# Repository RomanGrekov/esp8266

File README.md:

# ESPboard - esp8266 based home atomation board

Contain next functions:
  1. Get temperature and relative humidity from DHT22 sensor
  2. Manage GPIO port to turn/off solid state relay
  3. Send and receive data with mqtt protocol.

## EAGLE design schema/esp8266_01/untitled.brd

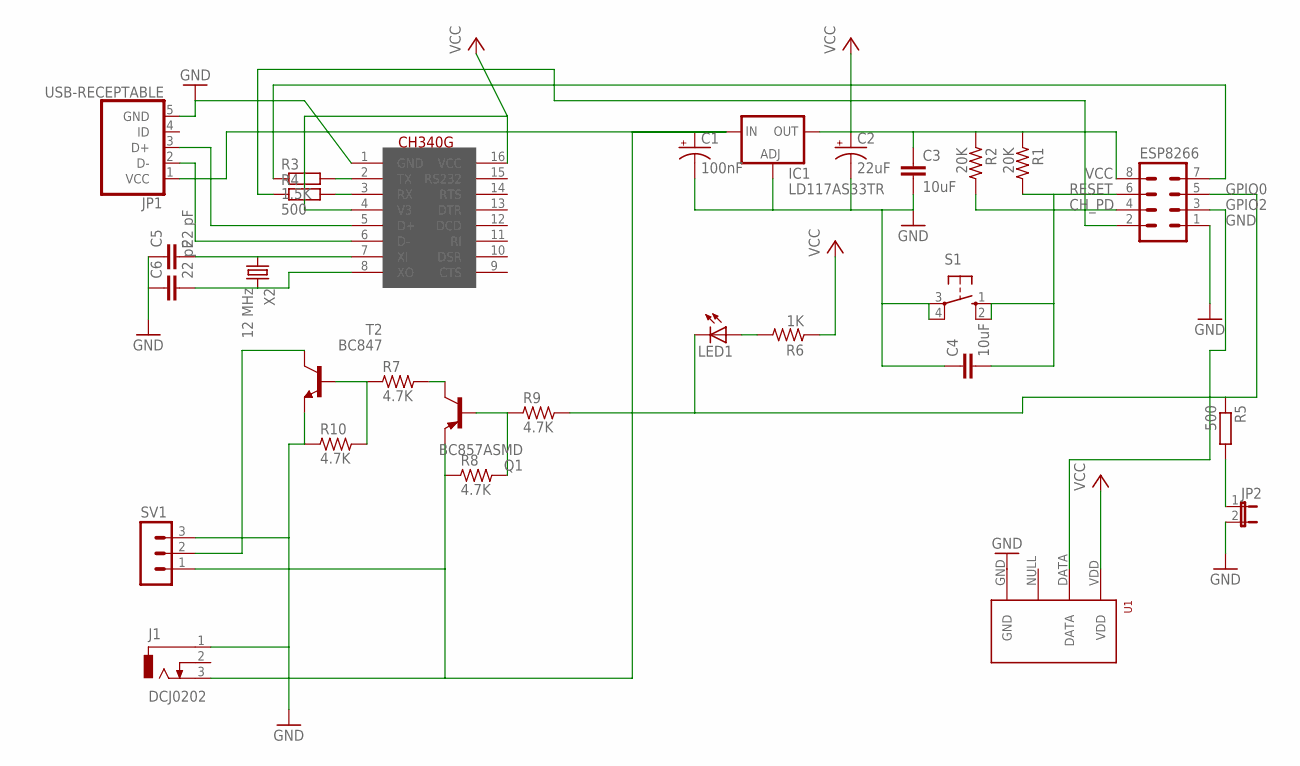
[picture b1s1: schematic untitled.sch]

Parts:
C1: 100nF; E2-4
C2: 22uF; E2-4
C3: 10uF; C0805
C4: 10uF; C5B2.5
C5, C6: 22 pF; C0805
ESP8266: MA04-2
IC1: LD117AS33TR; SOT223
J1: DCJ0202
JP1: USB-RECEPTABLE; FCI-10103594-0001LF
JP2: JP1E; JP1
LED1: LED3MM
Q1: BC857ASMD; SOT23-BEC
R1, R2: 20K; R0805
R3: 1.5K; R0805
R4: 500; R0805
R5: 500; 0204/5
R6: 1K; R0805
R7, R8, R9, R10: 4.7K; R0805
S1: 10-XX; B3F-10XX
SV1: MA03-1
T2: BC847; SOT23
U1: RHT03_DHT-22_AM2302; RHT03_DHT-22
U$1: CH340G; SOIC16
X2: 12 MHz; HC49

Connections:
CH_PD: ESP8266.4, R2.2
GND: C1.-, C2.-, C3.2, C4.1, C5.1, C6.1, ESP8266.1, IC1.1 (ADJ), J1.1, JP1.5 (GND), JP2.2, R10.1, S1.3, S1.4 (P1), SV1.3, T2.2 (E), U1.GND, U$1.1 (GND)
GPIO0: ESP8266.5, LED1.K (C), R5.1, R9.2
GPIO2: ESP8266.3, U1.DATA
unnamed: JP2.1, R5.2
unnamed: Q1.B, R8.2, R9.1
unnamed: Q1.C, R7.2
unnamed: C5.2, U$1.7 (XI), X2.1
unnamed: C6.2, U$1.8 (XO), X2.2
unnamed: JP1.2 (D-), U$1.6 (D-)
unnamed: JP1.3 (D+), U$1.5 (D+)
unnamed: LED1.A, R6.2
unnamed: ESP8266.7, R3.1
unnamed: R3.2, U$1.2 (TX)
unnamed: ESP8266.2, R4.1
unnamed: R4.2, U$1.3 (RX)
unnamed: R7.1, R10.2, T2.1 (B)
unnamed: SV1.2, T2.3 (C)
unnamed: C1.+, IC1.3 (IN), J1.3, JP1.1 (VCC), Q1.E, R8.1, SV1.1
RESET: C4.2, ESP8266.6, R1.2, S1.1 (S), S1.2 (S1)
VCC: C2.+, C3.1, ESP8266.8, IC1.4 (OUT), R1.1, R2.1, R6.1, U1.VDD, U$1.4 (V3), U$1.16 (VCC)

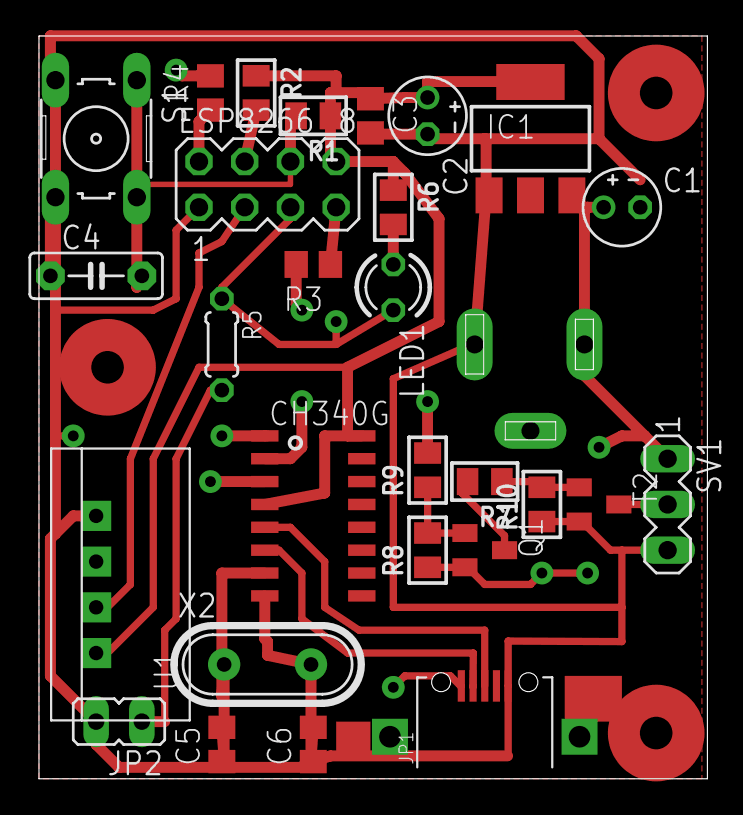
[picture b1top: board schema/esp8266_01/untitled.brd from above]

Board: 2 copper layers, 37.1 x 41.3 mm, 29 parts (1 on the bottom side), 21 nets.

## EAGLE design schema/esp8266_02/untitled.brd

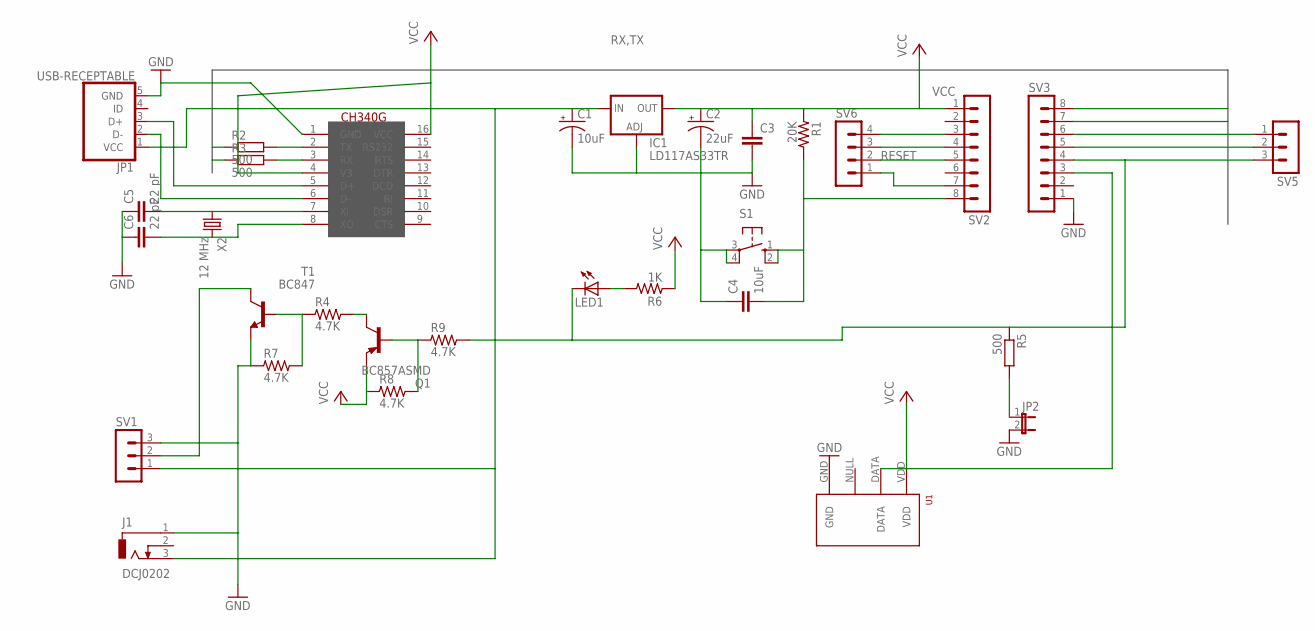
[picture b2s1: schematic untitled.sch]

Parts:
C1: 10uF; E2-4
C2: 22uF; E2-4
C3: C-EUC0805; C0805
C4: 10uF; C5B2.5
C5, C6: 22 pF; C0805
IC1: LD117AS33TR; SOT223
J1: DCJ0202
JP1: USB-RECEPTABLE; FCI-10103594-0001LF
JP2: JP1E; JP1
LED1: LED3MM
Q1: BC857ASMD; SOT23-BEC
R1: 20K; R0805
R2, R3, R5: 500; M0805
R4, R7, R8, R9: 4.7K; R0805
R6: 1K; R0805
S1: 10-XX; B3F-10XX
SV1, SV5: MA03-1
SV2, SV3: MA08-1
SV6: MA04-1
T1: BC847; SOT23
U1: RHT03_DHT-22_AM2302; RHT03_DHT-22
U$1: CH340G; SOIC16
X2: 12 MHz; HC49

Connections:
GND: C1.-, C2.-, C3.2, C4.1, C5.1, C6.1, IC1.1 (ADJ), J1.1, JP1.5 (GND), JP2.2, R7.1, S1.3, S1.4 (P1), SV1.3, SV3.1, T1.2 (E), U1.GND, U$1.1 (GND)
GPIO0: LED1.K (C), R5.1, R9.2, SV3.4, SV5.3
GPIO2: SV3.3, U1.DATA
unnamed: JP2.1, R5.2
unnamed: Q1.B, R8.2, R9.1
unnamed: Q1.C, R4.2
unnamed: C5.2, U$1.7 (XI), X2.1
unnamed: C6.2, U$1.8 (XO), X2.2
unnamed: JP1.2 (D-), U$1.6 (D-)
unnamed: JP1.3 (D+), U$1.5 (D+)
unnamed: LED1.A, R6.2
unnamed: SV2.7, SV6.1
unnamed: C1.+, IC1.3 (IN), J1.3, JP1.1 (VCC), SV1.1
unnamed: SV2.5, SV6.2
unnamed: SV2.4, SV6.3
unnamed: SV2.3, SV6.4
unnamed: R2.2, U$1.2 (TX)
unnamed: R3.2, U$1.3 (RX)
unnamed: R4.1, R7.2, T1.1 (B)
unnamed: SV3.6, SV5.1
unnamed: SV1.2, T1.3 (C)
unnamed: SV3.5, SV5.2
RESET: C4.2, R1.2, S1.1 (S), S1.2 (S1), SV2.8
RX: R3.1, SV3.8
TX: R2.1, SV3.7
VCC: C2.+, C3.1, IC1.4 (OUT), Q1.E, R1.1, R6.1, R8.1, SV2.1, U1.VDD, U$1.4 (V3), U$1.16 (VCC)

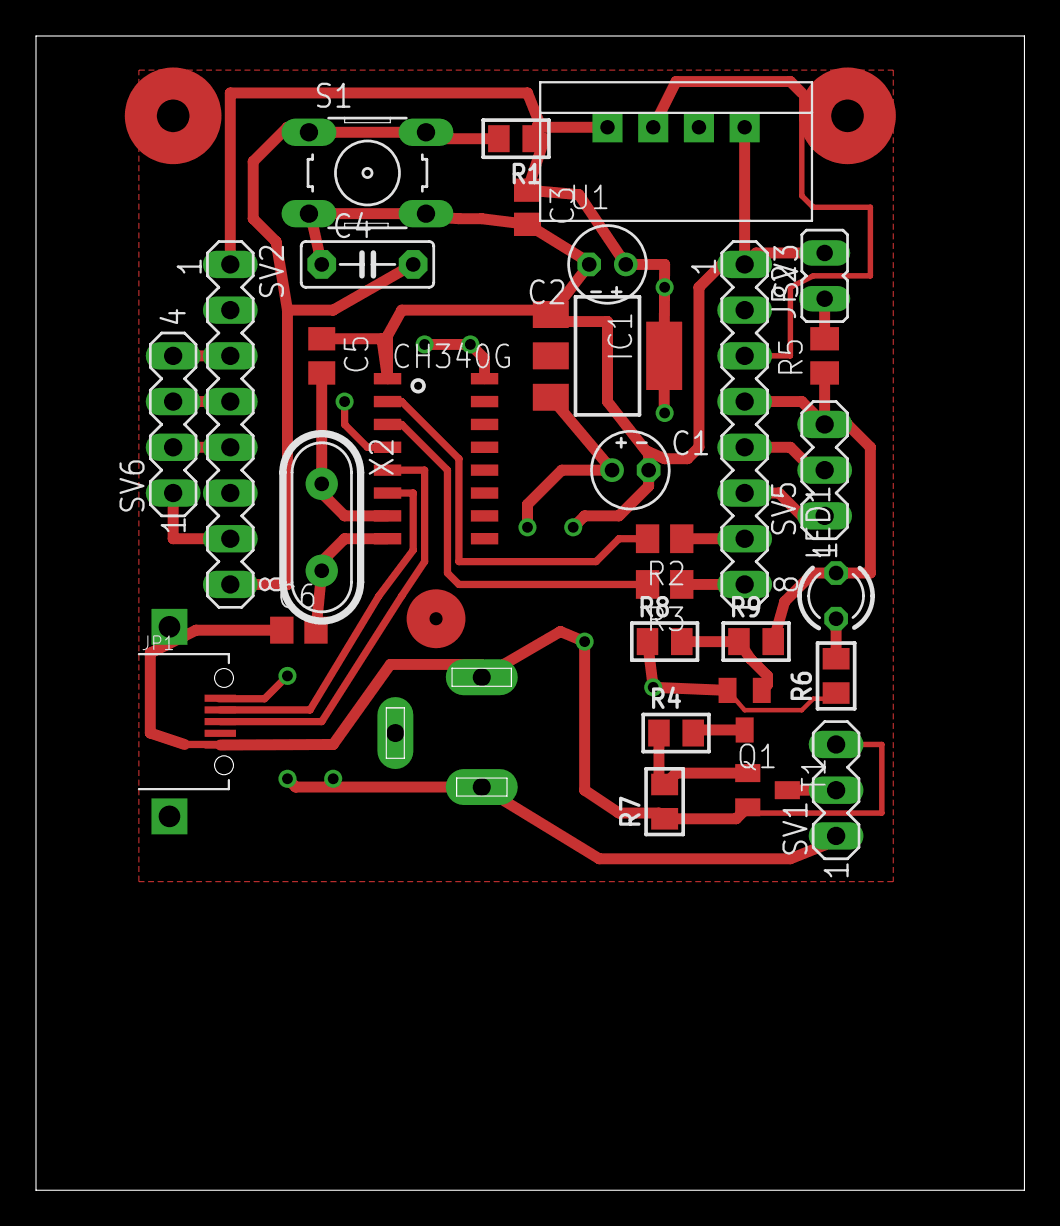
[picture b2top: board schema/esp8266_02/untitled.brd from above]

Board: 2 copper layers, 54.9 x 64.1 mm, 31 parts (1 on the bottom side), 26 nets.

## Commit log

2015-03-07 Added all
2015-03-09 Refactored code. To fit to memmory
2015-03-09 Fixed subscribe string
2015-03-09 Added ch340
2015-03-14 Added normal dht22 lib. Fixed known issues. looks like stable
2015-03-15 Added second variant of esp8266
2015-03-15 fixed power for usb-usart
2015-03-16 Fixed schema issues
2015-03-16 Normalaised code
2015-03-16 Moved dht22 in second version
2015-03-16 Minimised schema var 1
2015-03-19 Fixed all schemas. Just needed to change miscro USB sockets
2015-03-20 Finished ver 1.0 for both boards

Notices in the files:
parts and their libraries:
rc-master: Copyright (C) 2007, Bob Starr
